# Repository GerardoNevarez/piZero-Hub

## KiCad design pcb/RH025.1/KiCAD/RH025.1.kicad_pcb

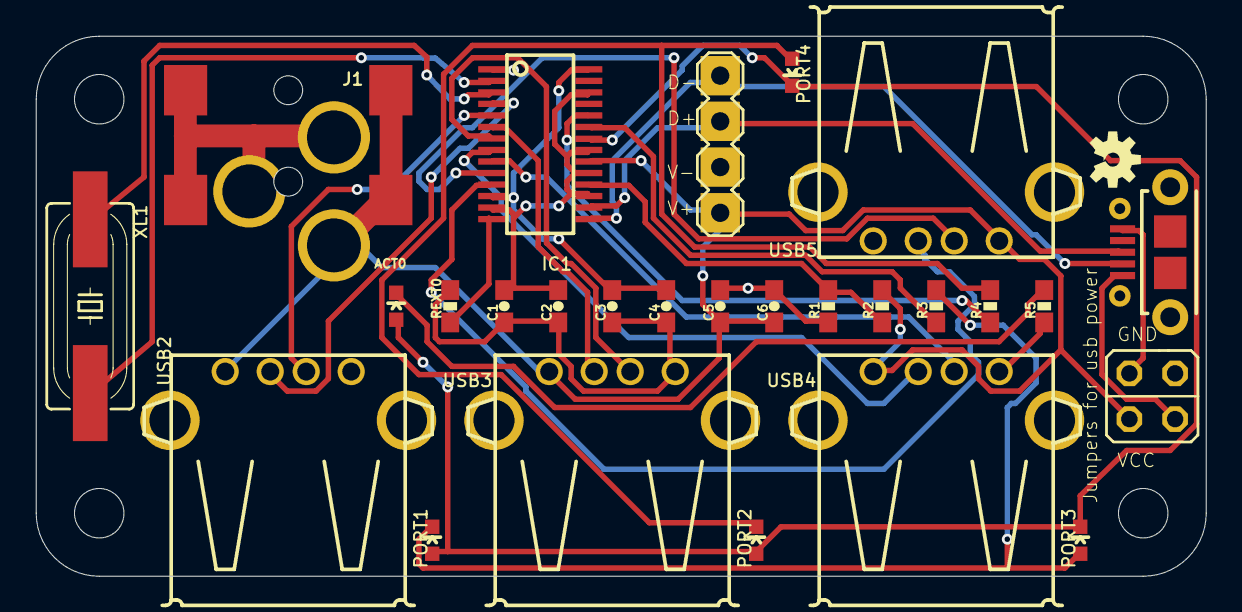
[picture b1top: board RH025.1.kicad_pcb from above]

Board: 2 copper layers, 65.0 x 30.0 mm, 32 parts (0 on the bottom side), 26 nets.

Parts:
@HOLE0, @HOLE1, @HOLE2, @HOLE3: (no value)
ACT0: LED-0603
C1, C3, C6: 0.1uF; CAP-0603
C2, C4, C5: 10uF; CAP-0603
IC1: FE1.1S; FE1.1S_SSOP-28
J1: POWER_JACKCOMBO; POWER_JACK_COMBO
JP1: JP2Q
PORT1, PORT2, PORT3, PORT4: LED-0603
R1: 100K; RES-0603
R2: 47K; RES-0603
R3, R4, R5: 330; RES-0603
REXT0: 2.7K; RES-0603
SV1: MA04-1
U$3: OSHW-LOGO-S
USB1: USBMICROB-PTH; USB-MICROB-TH
USB2, USB3, USB4, USB5: USBA-PTH; USB-A-F-PTH
XL1: 12MHz; HC49UP

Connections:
3V3: C1.1, C2.1, IC1.13, IC1.17, IC1.19, IC1.21, IC1.26
D+: IC1.16, SV1.3, USB1.D+
D-: IC1.15, SV1.4, USB1.D-
GND: C1.2, C2.2, C3.2, C4.2, C5.2, C6.2, IC1.1, J1.GND@1, JP1.4, R1.1, R5.1, REXT0.1, SV1.2, USB2.GND, USB3.GND, USB4.GND, USB5.GND
unnamed: IC1.14, REXT0.2
unnamed: JP1.2, USB1.VBUS
unnamed: JP1.3, USB1.GND
unnamed: PORT2.C, PORT4.A, R4.2
unnamed: IC1.2, XL1.2
unnamed: C3.1, C4.1, IC1.12, IC1.28
unnamed: IC1.3, XL1.1
unnamed: IC1.11, USB5.D+
unnamed: IC1.10, USB5.D-
unnamed: IC1.18, R1.2, R2.1
unnamed: IC1.9, USB4.D+
unnamed: IC1.8, USB4.D-
unnamed: IC1.7, USB3.D+
unnamed: IC1.6, USB3.D-
unnamed: IC1.5, USB2.D+
unnamed: IC1.4, USB2.D-
unnamed: PORT1.C, PORT3.A, R3.2
unnamed: ACT0.C, R5.2
unnamed: IC1.23, R3.1
unnamed: IC1.24, R4.1
unnamed: ACT0.A, IC1.22, PORT1.A, PORT2.A, PORT3.C, PORT4.C
VBUS: C5.1, C6.1, IC1.20, J1.POWER, JP1.1, R2.2, SV1.1, USB2.VBUS, USB3.VBUS, USB4.VBUS, USB5.VBUS

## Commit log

2023-02-13 Move EAGLE files to their own path
2023-02-13 Add KiCAD6 imported project
2023-02-14 Actually Add KiCAD6 imported project _(was KiCAD 5)_
